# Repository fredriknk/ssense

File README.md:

# Mina Soilsense

Open hardware for a Zigbee nrf52833 soil moisture probe, It is designed for using M3 stainless steel rods as probes screwed into the headers H1,H2,H3. It is designed to run on a 3.6v AA SAFT battery, average current is in the sub uA range when sampling 5 times per hour. So battery life should be in the range of 5-10 years. It has one 75mhz probe, one 1mhz probe (Variable frequency, so the plan is to do a frequency sweep with this to determine electrical conductivity in the medium) and a ground probe. It allso features a NFC coil, to pair the sensor with a gateway. And a temp sensor. 

Check out the ibom tool for component placement and hand soldering
[Assembly IBOM](https://htmlpreview.github.io/?https://raw.githubusercontent.com/fredriknk/ssense/main/DOCUMENTATION/ibom.html)

[PCB layout](./DOCUMENTATION/Board.pdf)

[SCHEMATIC](./DOCUMENTATION/Schematic.pdf)

## RF Testing

The antenna is simulated and optimized in matlab with [optimization script](https://github.com/fredriknk/antennasimulation) a theoretical -44dB S11, Actual measured S11 on the RF blanks is -26dB with a 0.5pF shunt capacotor soldered to L7 and a 0R resistor at C23. I left the antenna 1mm too long for tuning, but -26db is good enough for me. 

## Production run 1

Prototype produced at Eurocircuits

## Front

## Back

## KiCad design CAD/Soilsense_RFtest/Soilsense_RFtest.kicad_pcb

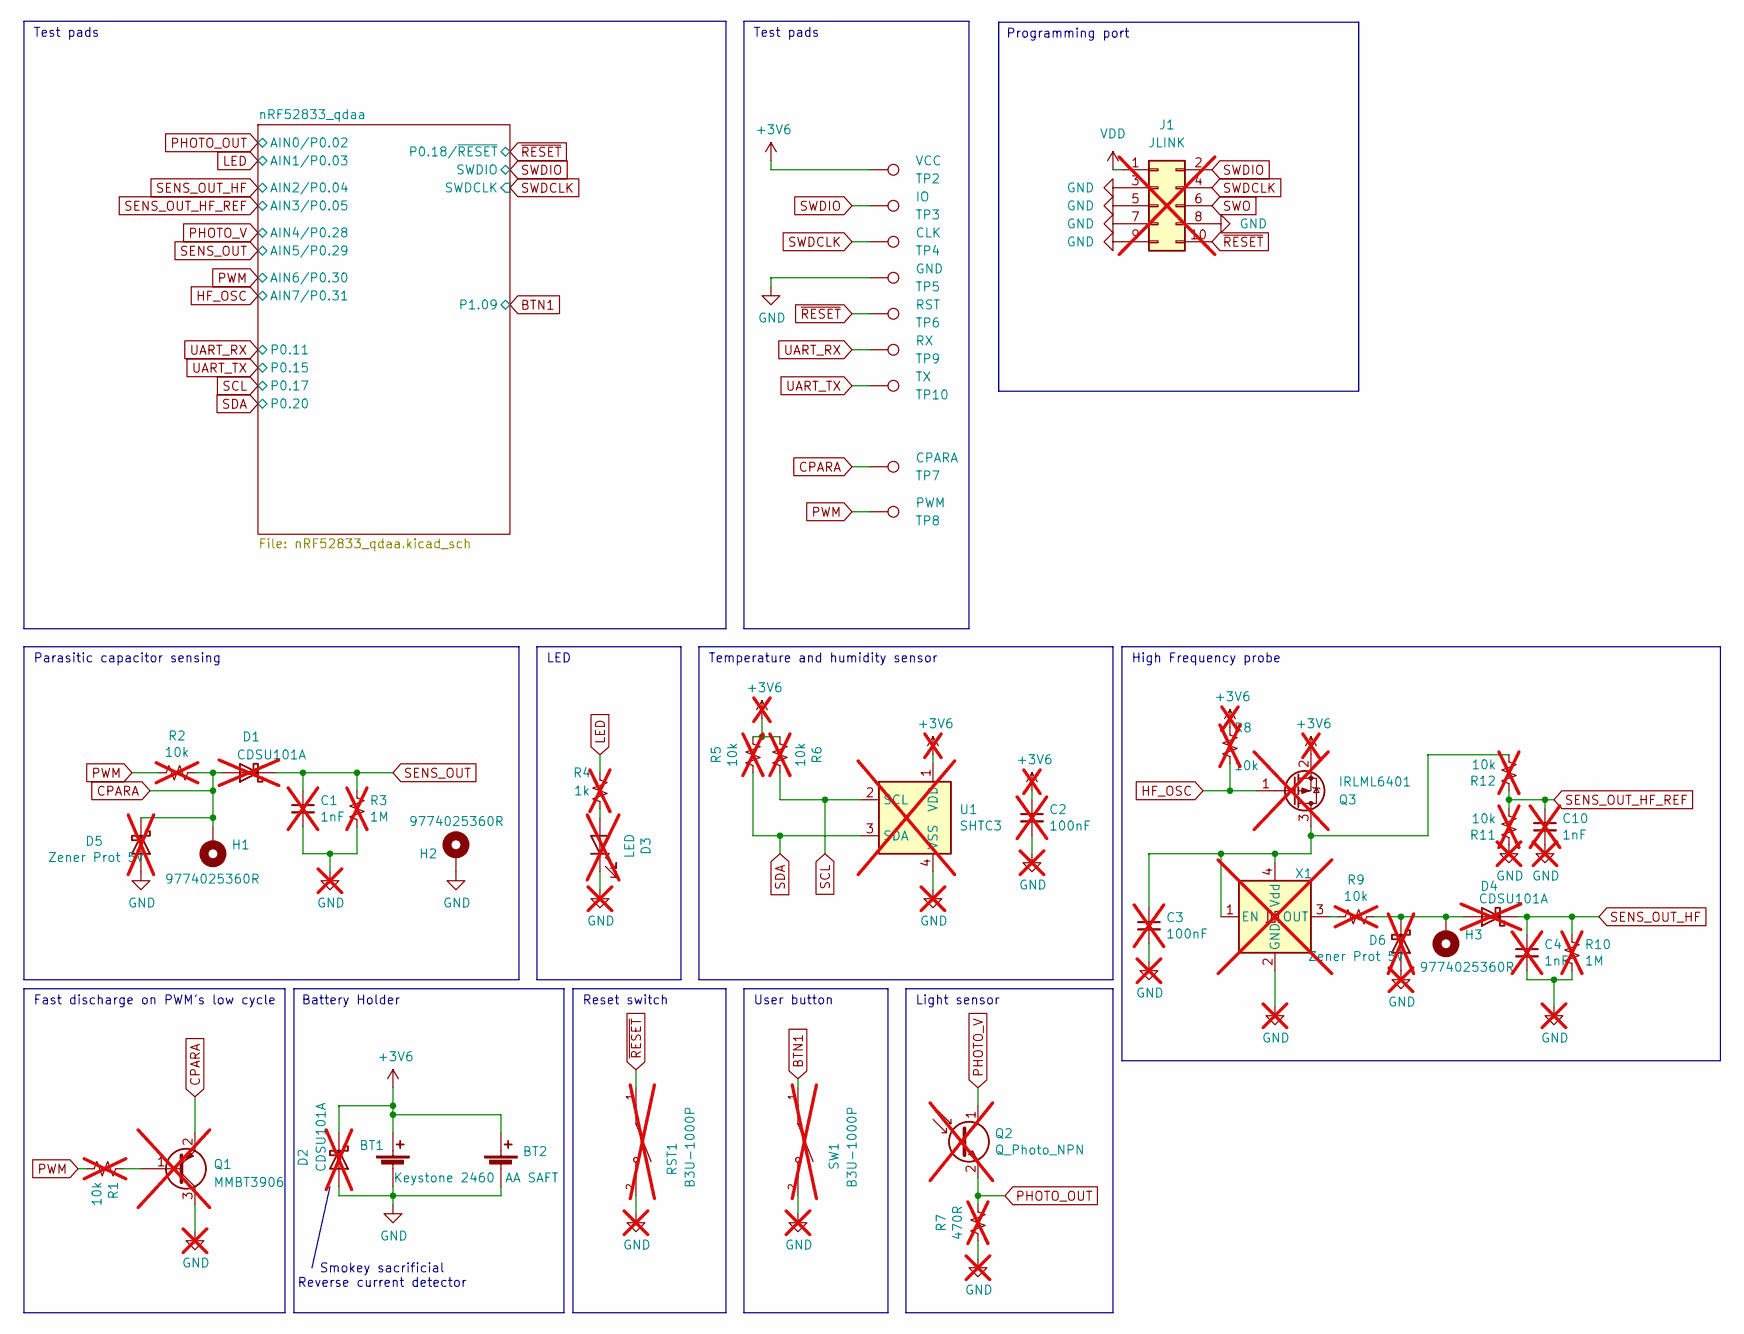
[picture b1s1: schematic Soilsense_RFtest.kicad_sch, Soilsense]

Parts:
BT1: Keystone 2460; BatteryHolder_Keystone_2460_1xAA; MPN 2460
BT2: AA SAFT; MPN LS14500 / SL760
C1, C4, C10: 1nF; C_0402_1005Metric; not fitted
C2, C3: 100nF; C_0402_1005Metric; not fitted
D1, D2, D4: CDSU101A; D_SOD-523; MPN CDSU101A; not fitted
D3: LED; LED_0603_1608Metric; MPN LG L29K-G2J1-24-Z; not fitted
D5, D6: Zener Prot 5V; D_SOD-523; MPN EDZVT2R5.1B; not fitted
H1, H2, H3: 9774025360R; Mounting_Wuerth_WA-SMSI-M3_H2.5mm_9774025360; MPN 9774025360R
J1: JLINK; SEXY_pinpogo; not fitted
Q1: MMBT3906; SOT-23; MPN MMBT3906-7-F; not fitted
Q2: Q_Photo_NPN; PHOTOTRANS_1708Metric; MPN ALS-PT19-315C/L177/TR8; not fitted
Q3: IRLML6401; SOT-23; MPN IRLML6401; not fitted
R1, R5, R6, R8, R11, R12: 10k; R_0402_1005Metric; not fitted
R2, R9: 10k; R_0603_1608Metric; not fitted
R3, R10: 1M; R_0402_1005Metric; not fitted
R4: 1k; R_0402_1005Metric; not fitted
R7: 470R; R_0402_1005Metric; not fitted
RST1: B3U-1000P; SW_SPST_B3U-1000P-B; MPN B3U-1000P-B; not fitted
SW1: B3U-1000P; SW_SPST_B3U-1000P-B; MPN B3U-1000P-B; not fitted
TP2: VCC; TestPoint_Pad_D1.0mm
TP3: IO; TestPoint_Pad_D1.0mm
TP4: CLK; TestPoint_Pad_D1.0mm
TP5: GND; TestPoint_Pad_D1.0mm
TP6: RST; TestPoint_Pad_D1.0mm
TP7: CPARA; TestPoint_Pad_D1.0mm
TP8: PWM; TestPoint_Pad_D1.0mm
TP9: RX; TestPoint_Pad_D1.0mm
TP10: TX; TestPoint_Pad_D1.0mm
U1: SHTC3; Sensirion_DFN-4-1EP_2x2mm_P1mm_EP0.7x1.6mm; MPN SHTC3; not fitted
X1: KC3225K75.0000C1GE00; Oscillator_SMD_SeikoEpson_SG8002CE-4Pin_3.2x2.5mm; MPN KC3225K75.0000C1GE00; not fitted

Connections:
+3V6: BT1.1 (+), BT2.1 (+), C2.1, D2.1 (K), J1.1, Q3.2 (S), R5.2, R6.1, R8.1, TP2.1, U1.1 (VDD); also elsewhere on the board
BTN1: SW1.1; also elsewhere on the board
CPARA: D1.2 (A), D5.1 (K), H1.1, Q1.2 (E), R2.2, TP7.1
GND: BT1.2 (-), BT2.2 (-), C1.2, C2.2, C3.2, C4.2, C10.2, D2.2 (A), D3.1 (K), D5.2 (A), D6.2 (A), H2.1, J1.3, J1.5, J1.7, J1.8, J1.9, Q1.3 (C), R3.2, R7.1, R10.2, R11.1, RST1.2, SW1.2, TP5.1, U1.4 (VSS), X1.2 (GND); also elsewhere on the board
HF_OSC: Q3.1 (G), R8.2; also elsewhere on the board
LED: R4.2; also elsewhere on the board
unnamed: D3.2 (A), R4.1
unnamed: D4.2 (A), D6.1 (K), H3.1, R9.2
unnamed: Q1.1 (B), R1.1
unnamed: C3.1, Q3.3 (D), R12.2, X1.1 (EN), X1.4 (Vdd)
unnamed: R9.1, X1.3 (OUT)
PHOTO_OUT: Q2.2 (E), R7.2; also elsewhere on the board
PHOTO_V: Q2.1 (C); also elsewhere on the board
PWM: R1.2, R2.1, TP8.1; also elsewhere on the board
SCL: R6.2, U1.2 (SCL); also elsewhere on the board
SDA: R5.1, U1.3 (SDA); also elsewhere on the board
SENS_OUT: C1.1, D1.1 (K), R3.1; also elsewhere on the board
SENS_OUT_HF: C4.1, D4.1 (K), R10.1; also elsewhere on the board
SENS_OUT_HF_REF: C10.1, R11.2, R12.1; also elsewhere on the board
SWDCLK: J1.4, TP4.1; also elsewhere on the board
SWDIO: J1.2, TP3.1; also elsewhere on the board
SWO: J1.6
UART_RX: TP9.1; also elsewhere on the board
UART_TX: TP10.1; also elsewhere on the board
~RESET: J1.10, RST1.1, TP6.1; also elsewhere on the board

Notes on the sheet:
Reset switch
Fast discharge on PWM’s low cycle
Temperature and humidity sensor
Test pads
Smokey sacrificial Reverse current detector
Programming port
Light sensor
Battery Holder
High Frequency probe
User button
LED
Parasitic capacitor sensing

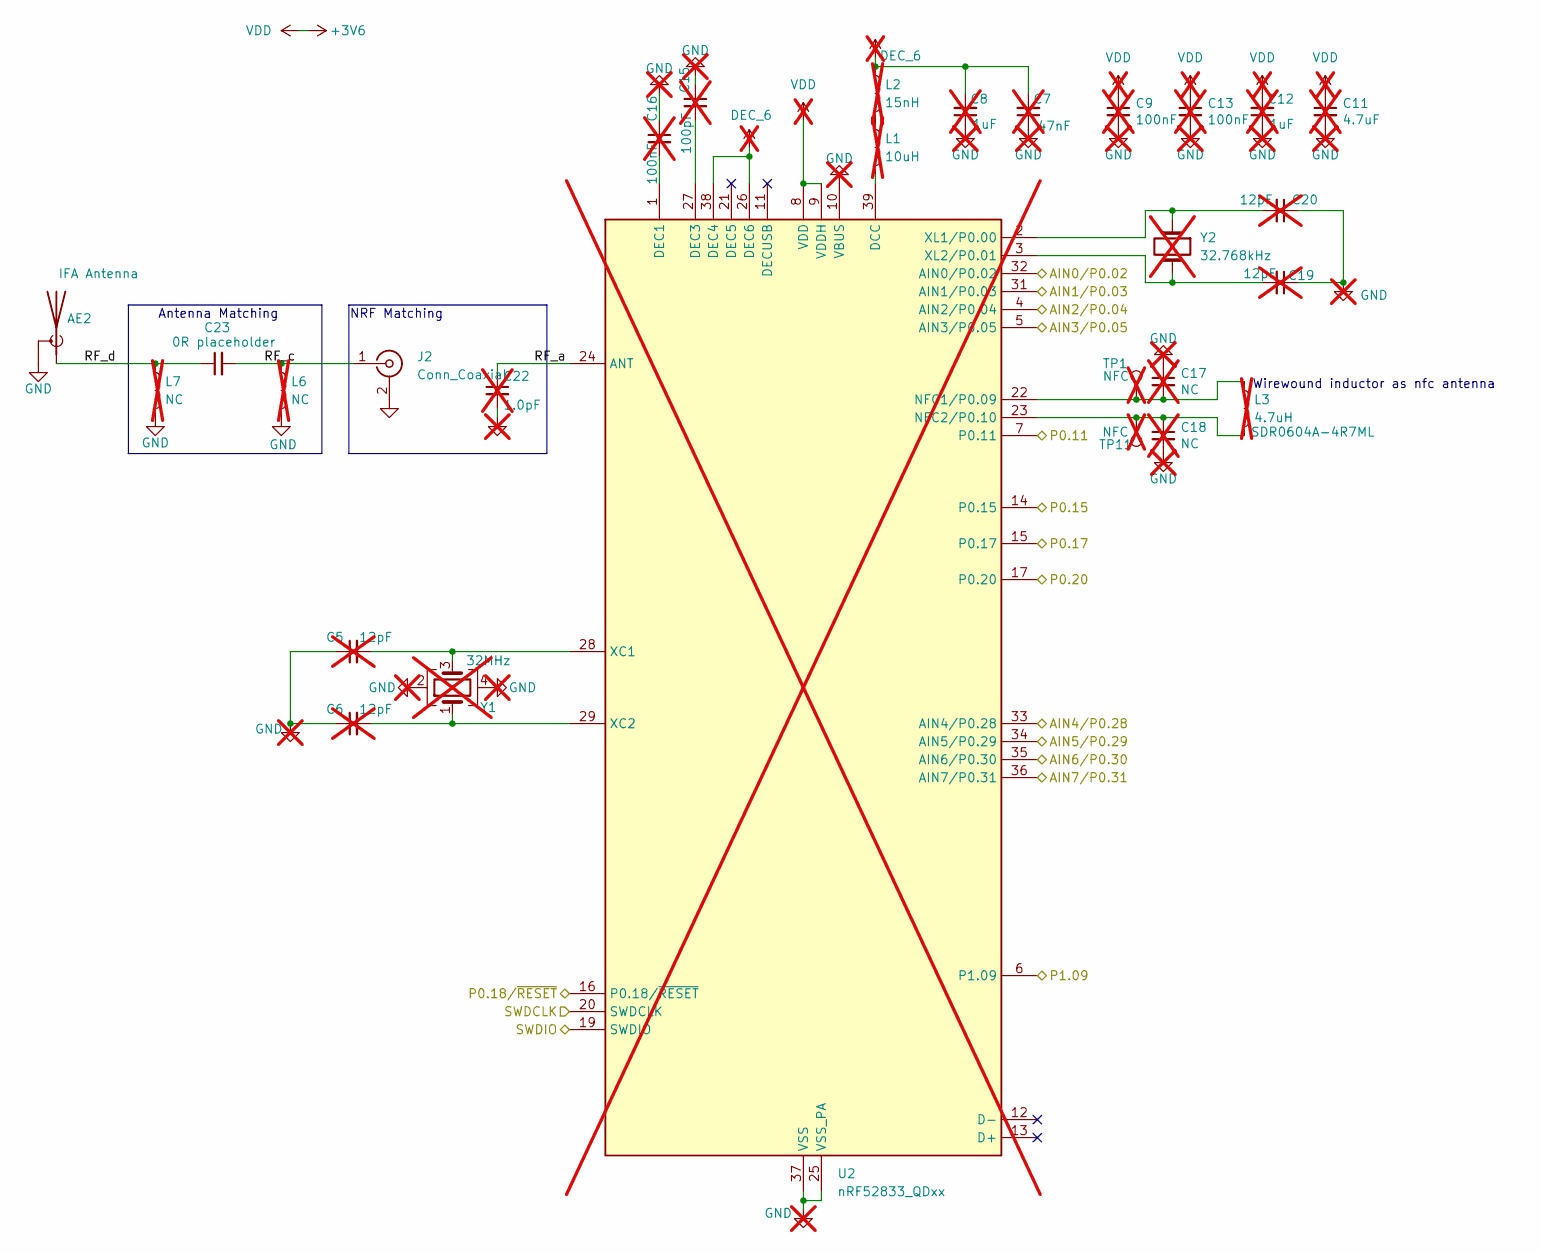
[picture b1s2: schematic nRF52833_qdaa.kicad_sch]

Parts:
AE2: IFA Antenna; IFA-0.12mm
C5, C6, C19, C20: 12pF; C_0402_1005Metric; not fitted
C7: 47nF; C_0402_1005Metric; not fitted
C8, C12: 1uF; C_0402_1005Metric; not fitted
C9, C13, C16: 100nF; C_0402_1005Metric; not fitted
C11: 4.7uF; C_0603_1608Metric; not fitted
C15: 100pF; C_0402_1005Metric; not fitted
C17, C18: NC; C_0402_1005Metric; not fitted
C22: 1.0pF; C_0402_1005Metric; MPN GJM1555C1H1R0WB01D; not fitted
C23: 0R placeholder; C_0603_1608Metric
J2: Conn_Coaxial; U.FL_Hirose_U.FL-R-SMT-1_Vertical
L1: 10uH; L_0603_1608Metric; not fitted
L2: 15nH; L_0402_1005Metric; not fitted
L3: 4.7uH; L_Bourns_SDSS604A; MPN SDR0604A-4R7ML; not fitted
L6, L7: NC; L_0603_1608Metric; not fitted
TP1, TP11: NFC; TestPoint_Pad_D1.0mm; not fitted
U2: nRF52833_QDxx; QFN-40-1EP_5x5mm_P0.4mm_EP3.6x3.6mm_ThermalVias; MPN nRF52833_QDAA; not fitted
Y1: 32MHz; Crystal_SMD_2016-4Pin_2.0x1.6mm; MPN XRCGB32M000F2P01R0; not fitted
Y2: 32.768kHz; Crystal_SMD_2012-2Pin_2.0x1.2mm; MPN CM8V-T1A-32.768KHZ-9PF-20PPM-TA-QC; not fitted

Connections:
+3V6: C9.1, C11.1, C12.2, C13.1, U2.8 (VDD), U2.9 (VDDH), U2.18 (VDD), U2.30 (VDD), U2.40 (VDD); also elsewhere on the board
/nRF52833_qdaa/RF_a: C22.1, U2.24 (ANT)
/nRF52833_qdaa/RF_c: C23.2, J2.1 (In), L6.1
/nRF52833_qdaa/RF_d: AE2.1 (A), C23.1, L7.1
BTN1: U2.6 (P1.09); also elsewhere on the board
DEC_6: C7.2, C8.2, L2.1, U2.26 (DEC6), U2.38 (DEC4)
GND: AE2.2 (Shield), C5.1, C6.1, C7.1, C8.1, C9.2, C11.2, C12.1, C13.2, C15.1, C16.1, C17.1, C18.2, C19.1, C20.1, C22.2, J2.2 (Ext), L6.2, L7.2, U2.10 (VBUS), U2.25 (VSS_PA), U2.37 (VSS), U2.41 (VSS), Y1.2, Y1.4; also elsewhere on the board
HF_OSC: U2.36 (AIN7/P0.31); also elsewhere on the board
LED: U2.31 (AIN1/P0.03); also elsewhere on the board
unnamed: L1.1, L2.2
unnamed: L1.2, U2.39 (DCC)
unnamed: C16.2, U2.1 (DEC1)
unnamed: C15.2, U2.27 (DEC3)
unnamed: C17.2, L3.1, TP1.1, U2.22 (NFC1/P0.09)
unnamed: C18.1, L3.2, TP11.1, U2.23 (NFC2/P0.10)
unnamed: C5.2, U2.28 (XC1), Y1.3
unnamed: C6.2, U2.29 (XC2), Y1.1
unnamed: C20.2, U2.2 (XL1/P0.00), Y2.1
unnamed: C19.2, U2.3 (XL2/P0.01), Y2.2
PHOTO_OUT: U2.32 (AIN0/P0.02); also elsewhere on the board
PHOTO_V: U2.33 (AIN4/P0.28); also elsewhere on the board
PWM: U2.35 (AIN6/P0.30); also elsewhere on the board
SCL: U2.15 (P0.17); also elsewhere on the board
SDA: U2.17 (P0.20); also elsewhere on the board
SENS_OUT: U2.34 (AIN5/P0.29); also elsewhere on the board
SENS_OUT_HF: U2.4 (AIN2/P0.04); also elsewhere on the board
SENS_OUT_HF_REF: U2.5 (AIN3/P0.05); also elsewhere on the board
SWDCLK: U2.20 (SWDCLK); also elsewhere on the board
SWDIO: U2.19 (SWDIO); also elsewhere on the board
UART_RX: U2.7 (P0.11); also elsewhere on the board
UART_TX: U2.14 (P0.15); also elsewhere on the board
~RESET: U2.16 (P0.18/~RESET); also elsewhere on the board

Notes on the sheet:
Wirewound inductor as nfc antenna
NRF Matching
Antenna Matching

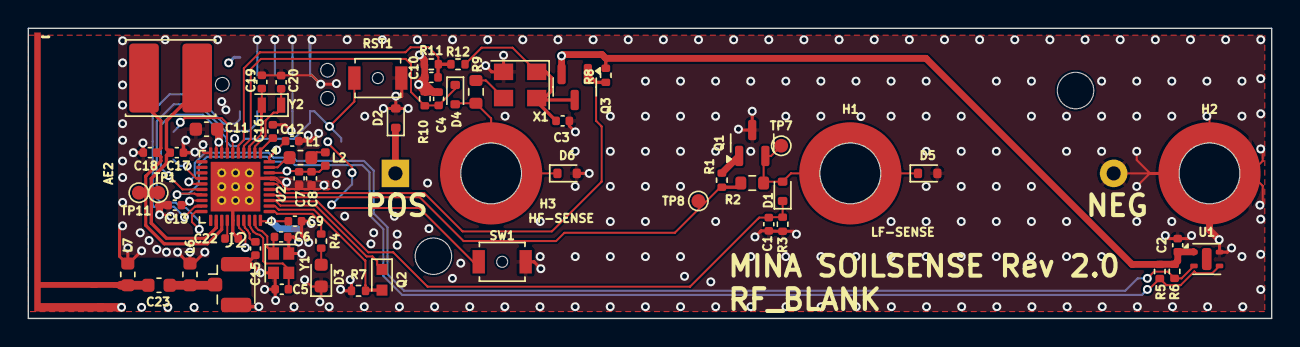
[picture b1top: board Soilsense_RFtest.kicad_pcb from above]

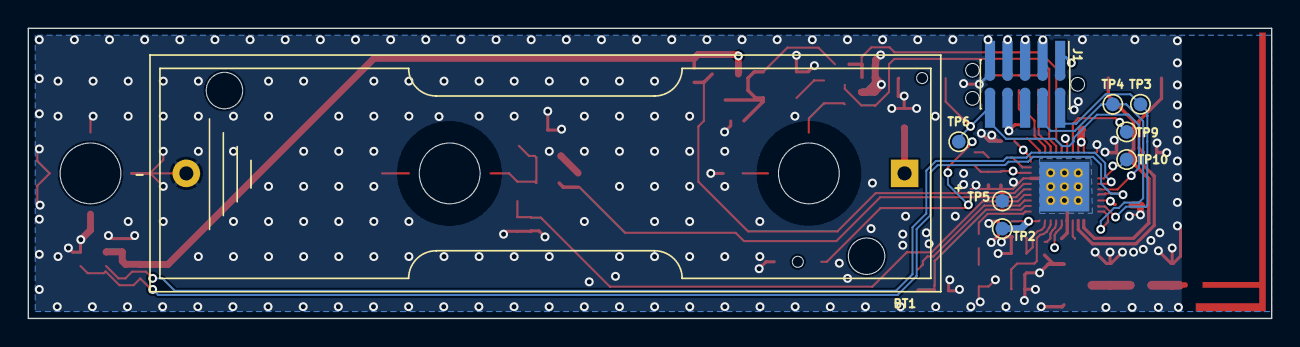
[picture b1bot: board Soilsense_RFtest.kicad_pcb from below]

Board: 4 copper layers, 90.0 x 21.0 mm, 72 parts (9 on the bottom side), 38 nets.

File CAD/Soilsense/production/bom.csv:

Designator,Footprint,Quantity,Value,LCSC Part #
BT1,BatteryHolder_Keystone_2460_1xAA,1,Keystone 2460,2460
"C1, C10, C4",0402,3,1nF,
C11,0603,1,4.7uF,
"C12, C8",0402,2,1uF,
"C13, C16, C2, C3, C9",0402,5,100nF,
C15,0402,1,100pF,
"C19, C20, C5, C6",0402,4,12pF,
C21,0402,1,1.2pF,
C22,0402,1,1.0pF,
C23,0603,1,0R placeholder,
C7,0402,1,47nF,
"D1, D2, D4",D_SOD-523,3,CDSU101A,CDSU101A
D3,0603,1,LED,
"D5, D6",D_SOD-523,2,Zener Prot 5V,EDZVT2R5.1B
"H1, H2, H3",Mounting_Wuerth_WA-SMSI-M3_H2.5mm_9774025360,3,9774025360R, 9774025360R
J1,SEXY_pinpogo,1,JLINK,
L1,0603,1,10uH,
L2,0402,1,15nH,
L3,L_Bourns_SDSS604A,1,4.7uH,SDR0604A-4R7ML
L4,0402,1,2.2nH,LQW15AN2N2C80D
L5,0402,1,4.7nH,LQW15AN4N7C80D
Q1,SOT-23,1,MMBT3906,
Q2,PHOTOTRANS_1708Metric,1,Q_Photo_NPN,ALS-PT19-315C/L177/TR8
Q3,SOT-23,1,IRLML6401,IRLML6401
"R1, R11, R12, R5, R6, R8",0402,6,10k,
"R10, R3",0402,2,1M,
"R2, R9",0603,2,10k,
R4,0402,1,1k,
R7,0402,1,470R,
"RST1, SW1",SW_SPST_B3U-1000P-B,2,B3U-1000P,
U1,Sensirion_DFN-4-1EP_2x2mm_P1mm_EP0.7x1.6mm,1,SHTC3,
U2,QFN-40-1EP_5x5mm_P0.4mm_EP3.6x3.6mm_ThermalVias,1,nRF52833_QDxx,nRF52833_QDAA
X1,Oscillator_SMD_SeikoEpson_SG8002CE-4Pin_3.2x2.5mm,1,KC3225K75.0000C1GE00,KC3225K75.0000C1GE00
Y1,Crystal_SMD_2016-4Pin_2.0x1.6mm,1,32MHz,XRCGB32M000F2P01R0
Y2,Crystal_SMD_2012-2Pin_2.0x1.2mm,1,32.768kHz,CM8V-T1A-32.768KHZ-9PF-20PPM-TA-QC

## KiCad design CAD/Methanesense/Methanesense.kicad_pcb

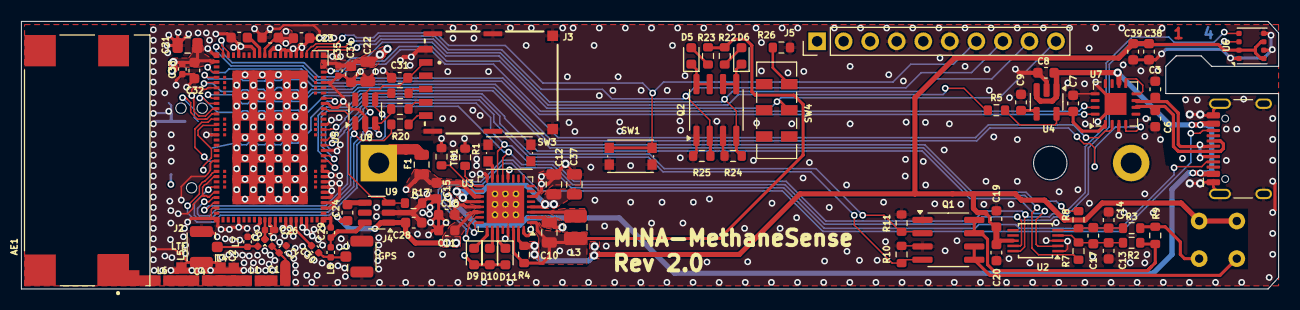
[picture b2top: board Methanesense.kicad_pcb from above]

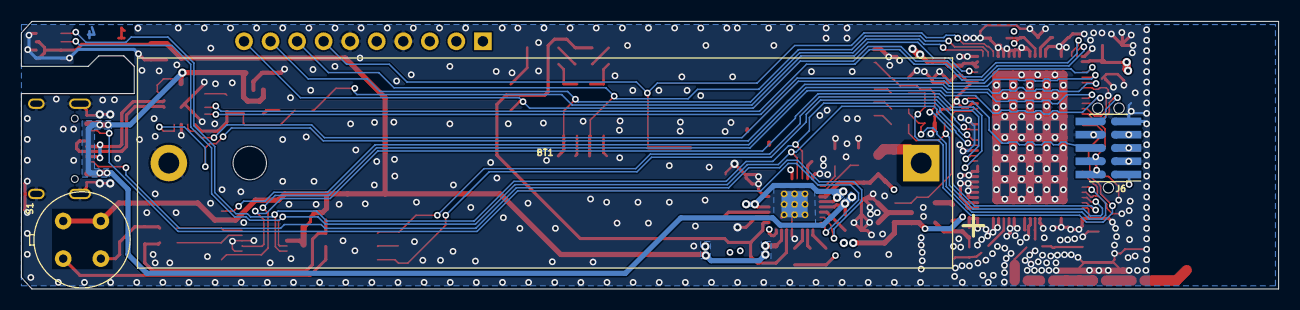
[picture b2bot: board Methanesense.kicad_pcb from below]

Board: 4 copper layers, 120.3 x 25.6 mm, 94 parts (3 on the bottom side), 72 nets.

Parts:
AE1: NN02-220; XCVR_NN02-220
BT1: BH-18650-PC2; BatteryHolder_MPD_BH-18650-PC2
C1, C2: 1.7pF; C_0603_1608Metric
C3, C6: 47pF; C_0603_1608Metric
C4: 8.5pF; C_0603_1608Metric
C5, C26, C27, C33, C35: 15pF; C_0402_1005Metric_Sqr
C7, C8, C9, C11, C16, C17, C20, C28, C31, C39: 1uF; C_0603_1608Metric
C10, C12, C37: 10uF; C_0805_2012Metric
C13, C14, C19, C32, C34, C36, C38: 0.1uF; C_0603_1608Metric
C15, C23, C25: 4.7uF; C_0603_1608Metric
C21, C22: 47uF; C_0805_2012Metric
C24: 1nF; C_0603_1608Metric
C29, C30: 56pF; C_0402_1005Metric_Sqr
D5, D6, D9, D10, D11: LED; LED_0603_1608Metric
F1: 0805L110WR; Fuse_0805_2012Metric
J1: USB_C_Receptacle_USB2.0_14P; USB_C_Receptacle_HCTL_HC-TYPE-C-16P-01A
J2, J4: HIROSE ELECTRIC U.FL-R-SMT-1; U.FL_Hirose_U.FL-R-SMT-1_Vertical
J3: 693043020611
J5: Conn_01x10_Pin; PinHeader_1x10_P2.54mm_Vertical
J6: JLINK; SEXY_pinpogo
L1: 2.3nH; L_0603_1608Metric
L2, L7: 39NH; C_0402_1005Metric_Sqr
L3: 2.2uH; L_1008_2520Metric
L4: NP; L_0603_1608Metric
L5: 7.5NH; L_0603_1608Metric
L6: 1.6nH; L_0603_1608Metric
L8: 68 nH; C_0402_1005Metric_Sqr
Q1, Q2: FDS6898A; SOIC-8_3.9x4.9mm_P1.27mm
R1: 68k; R_0603_1608Metric
R2, R3: 470R; R_0603_1608Metric
R4, R5, R7, R8: 0R; R_0603_1608Metric
R9: <2k; R_0603_1608Metric
R10, R11, R17, R24, R25: 1M; R_0603_1608Metric
R18, R19, R20, R22, R23: 100R; R_0603_1608Metric
R26: 1k; R_0603_1608Metric
S1: TGS8410
SW1, SW3: KMR223NGLFG; SW_Push_1P1T_NO_CK_KMR2
SW4: JS202011JCQN; SW_DPDT_CK_JS202011JCQN
TH1: 10k NTC; R_0603_1608Metric
U2: ADS1115IDGS; TSSOP-10_3x3mm_P0.5mm
U3: nPM1300-QEXX; QFN-32-1EP_5x5mm_P0.5mm_EP3.6x3.6mm_ThermalVias
U4: AP7331-20WG-7; SOT-23-5
U5: nRF9160-SICA; LGA_9160_16.0x10.5mm
U6: BME680; Bosch_LGA-8_3x3mm_P0.8mm_ClockwisePinNumbering
U7: FT230XQ; QFN-16-1EP_4x4mm_P0.65mm_EP2.1x2.1mm
U8: USBLC6-4SC6; SOT-23-6
U9: TPS22917DBV; SOT-23-6

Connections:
+1V8SIM: C31.1, J3.C1 (VCC), U5.49 (SIM_1V8), U8.5 (VBUS)
+2V0: C10.1, C23.1, C36.1, J5.1, J6.1, L3.1, R4.1, R22.1, R23.2, U3.1 (VOUT1), U3.12 (VDDIO), U3.30 (LSIN2/VINLDO2), U5.12 (VDD_GPIO)
+2V0SW: C19.1, C20.1, C38.1, C39.1, R4.2, S1.3 (Rs+), S1.4 (Rh+), U2.8 (VDD), U3.31 (LSOUT2/VOUTLDO2), U6.2 (CSB), U6.6 (VDDIO), U6.8 (VDD)
+5V: C11.1, C21.1, C22.1, C24.1, C28.1, C32.1, C33.1, C34.1, C35.1, J5.2, U3.22 (VBUSOUT), U5.22 (VDD2), U5.101 (ENABLE), U5.102 (VDD1), U9.1 (VIN)
+5VL: C8.1, C16.1, J1.A4 (VBUS), J1.A9 (VBUS), J1.B4 (VBUS), J1.B9 (VBUS), J5.5, U3.21 (VBUS), U4.1 (IN), U4.3 (EN), U7.10 (VCC)
+BATT: C15.1, F1.1, J5.3, U3.19 (VBAT)
/GAS_SENSOR/AIN0_: C13.2, C17.1, R2.1, R7.2, U2.4 (AIN0)
/GAS_SENSOR/AIN1_: C14.2, C17.2, R3.1, R8.1, U2.5 (AIN1)
/POWER/CC1: J1.A5 (CC1), U3.23 (CC1)
/POWER/CC2: J1.B5 (CC2), U3.24 (CC2)
/POWER/SW1: L3.2, U3.3 (SW1)
/POWER/USBDN: C3.2, J1.A7 (D-), J1.B7 (D-), U7.7 (USBDM)
/POWER/USBDP: C6.2, J1.A6 (D+), J1.B6 (D+), U7.6 (USBDP)
/POWER/VCCIOUSB: C7.1, R5.2, U4.5 (OUT), U7.1 (VCCIO)
/nrf9160/ANT: C5.1, C26.1, C27.1, U5.61 (ANT)
/nrf9160/GPS: C30.1, U5.67 (GPS)
/nrf9160/GPS_: C30.2, J4.1 (In), L8.1
AIN0: Q1.7 (D1), Q1.8 (D1), R2.2, R9.1
AIN1: R3.2, R9.2, S1.2 (Rs-)
COEX0: R17.2, U5.93 (COEX0), U9.3 (ON)
GND: BT1.2 (-), C2.2, C3.1, C6.1, C7.2, C8.2, C9.2, C10.2, C11.2, C12.2, C13.1, C14.1, C15.2, C16.2, C19.2, C20.2, C21.2, C22.2, C23.2, C25.2, C26.2, C28.2, C29.2, C31.2, C32.2, C33.2, C34.2, C35.2, C36.2, C37.2, C38.2, C39.2, J1.A1 (GND), J1.A12 (GND), J1.B1 (GND), J1.B12 (GND), J1.S1 (SHIELD), J2.2 (Ext), J3.C5 (GND), J3.S1, J3.S2, J3.S3, J3.S4, J3.S5, J3.S6, J4.2 (Ext), J5.4, J5.6, J6.3, J6.5, J6.7, J6.8, J6.9, L2.2, L4.2, L5.2, L7.2, Q1.1 (S1), Q1.3 (S2), Q2.1 (S1), Q2.3 (S2), R1.2, R10.1, R11.1, R17.1, R24.1, R25.1, R26.1, SW1.2, SW3.2, TH1.1, U2.1 (ADDR), U2.3 (GND), U3.2 (PVSS1), U3.6 (PVSS2), U3.16 (VSET2), U3.29 (LSOUT1/VOUTLDO1), U3.33 (AVSS), U4.2 (GND), U5.1 (GND_Shield), U5.5 (GND_Shield), U5.6 (GND_Shield), U5.7 (GND_Shield), U5.8 (GND_Shield), U5.9 (GND_Shield), U5.11 (GND_Shield), U5.14 (GND_Shield), U5.17 (GND_Shield), U5.21 (GND_Shield), U5.27 (GND_Shield), U5.31 (GND_Shield), U5.36 (GND_Shield), U5.41 (GND_Shield), U5.44 (GND_Shield), U5.47 (GND_Shield), U5.50 (GND_Shield), U5.52 (GND_Shield), U5.56 (GND_Shield), U5.60 (GND_Shield), U5.62 (GND_Shield), U5.63 (GND_Shield), U5.65 (GND_Shield), U5.66 (GND_Shield), U5.68 (GND_Shield), U5.69 (GND_Shield), U5.72 (GND_Shield), U5.74 (GND_Shield), U5.75 (GND_Shield), U5.76 (GND_Shield), U5.77 (GND_Shield), U5.78 (GND_Shield), U5.79 (GND_Shield), U5.80 (GND_Shield), U5.81 (GND_Shield), U5.82 (GND_Shield), U5.85 (GND_Shield), U5.90 (GND_Shield), U5.94 (GND_Shield), U5.98 (GND_Shield), U5.103 (VSS), U6.1 (GND), U6.5 (SDO), U6.7 (GND), U7.3 (GND), U7.13 (GND), U7.17 (GND), U8.2 (GND), U9.2 (GND)
unnamed: AE1.1 (A), L6.2
unnamed: BT1.1 (+), F1.2
unnamed: C1.1, C27.2, L2.1
unnamed: C1.2, L1.1
unnamed: C2.1, C4.1, L1.2, L4.1
unnamed: C4.2, L5.1, L6.1
unnamed: D5.2 (A), R23.1
unnamed: D5.1 (K), Q2.7 (D1), Q2.8 (D1)
unnamed: D6.2 (A), R22.2
unnamed: D6.1 (K), Q2.5 (D2), Q2.6 (D2)
unnamed: D9.1 (K), U3.25 (LED0)
unnamed: D10.1 (K), U3.26 (LED1)
unnamed: D11.1 (K), U3.27 (LED2)
unnamed: C5.2, J2.1 (In), L7.1
unnamed: J3.C3 (CLK), R19.1
unnamed: J3.C7 (I/O), R20.1
unnamed: J3.C2 (RST), R18.1
unnamed: Q1.5 (D2), Q1.6 (D2), S1.1 (Rh-)
unnamed: R26.2, SW4.1 (A)
unnamed: TH1.2, U3.18 (NTC)
unnamed: SW3.1, U3.15 (SHPHLD)
unnamed: R1.1, U3.17 (VSET1)
unnamed: C9.1, U4.4 (BP)
unnamed: C25.1, U5.13 (DEC0)
unnamed: U7.8 (3V3OUT), U7.9 (~RESET)
unnamed: C24.2, U9.4 (CT)
unnamed: C29.1, L8.2, U9.6 (VOUT)
P0.04: R5.1, U5.100 (P0.04)
P0.05: J5.9, Q2.4 (G2), R24.2, U5.2 (P0.05)
P0.06: J5.8, Q2.2 (G1), R25.2, U5.3 (P0.06)
P0.07: J5.7, SW1.1, U5.4 (P0.07)
P0.11: J5.10, SW4.2 (B), U5.19 (P0.11)
P0.12: U5.20 (P0.12), U7.15 (TXD)
P0.14/AIN1: U5.24 (P0.14/AIN1), U7.16 (~RTS)
P0.15/AIN2: U5.25 (P0.15/AIN2), U7.2 (RXD)
P0.16/AIN3: U5.26 (P0.16/AIN3), U7.4 (~CTS)
P0.18/AIN5: R8.2, U5.29 (P0.18/AIN5)
P0.19/AIN6: R7.1, U5.30 (P0.19/AIN6)
P0.26: U2.2 (ALERT/RDY), U5.83 (P0.26)
P0.27: Q1.2 (G1), R11.2, U5.84 (P0.27)
P0.28: U2.9 (SDA), U3.13 (SDA), U5.86 (P0.28), U6.3 (SDI)
P0.29: U2.10 (SCL), U3.14 (SCL), U5.87 (P0.29), U6.4 (SCK)
P0.31: Q1.4 (G2), R10.2, U5.89 (P0.31)
SIM_CLK: R19.2, U5.46 (SIM_CLK), U8.3 (I/O2)
SIM_IO: R20.2, U5.48 (SIM_IO), U8.1 (I/O1)
SIM_RST: R18.2, U5.43 (SIM_RST), U8.4 (I/O3)
SWDCLK: J6.4, U5.33 (SWDCLK)
SWDIO: J6.2, U5.34 (SWDIO)
SWO: J6.6, U5.95 (P0.00)
VSYS: C12.1, C37.1, D9.2 (A), D10.2 (A), D11.2 (A), U3.4 (PVDD), U3.20 (VSYS), U3.32 (VOUT2)
~RESET: J6.10, U5.32 (~RESET)

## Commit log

2024-08-15 NFC update
2024-08-15 Layout
2024-10-10 Small changes
2024-10-11 Rev 2.0
2024-10-11 RF-testing
2024-10-11 Added antenna script
2025-08-15 Fix: DRC Exclusions
